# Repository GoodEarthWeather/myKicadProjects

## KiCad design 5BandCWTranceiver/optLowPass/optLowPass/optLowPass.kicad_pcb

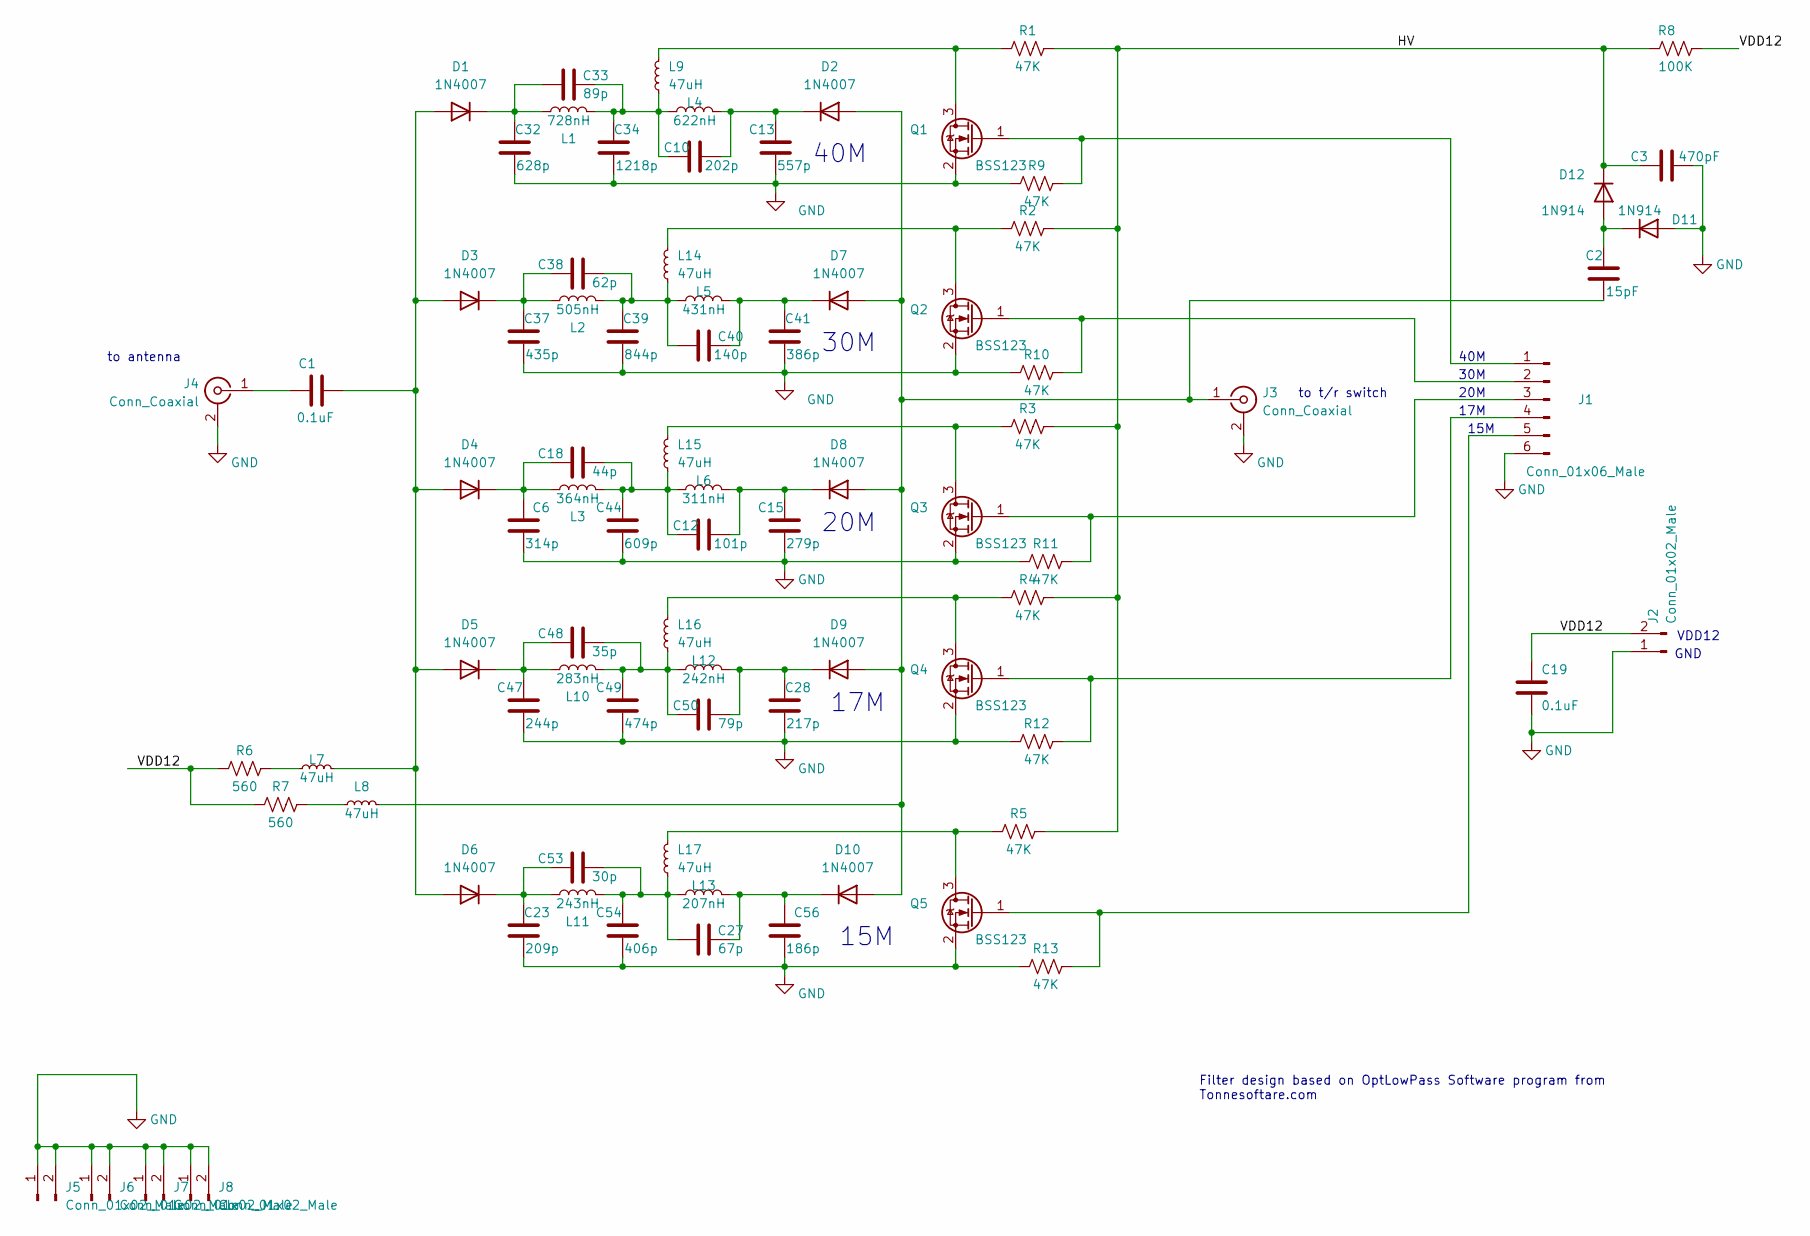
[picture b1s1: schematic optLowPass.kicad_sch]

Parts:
C1: 0.1uF; C_Disc_D4.3mm_W1.9mm_P5.00mm
C2: 15pF; C_Disc_D4.3mm_W1.9mm_P5.00mm
C3: 470pF; C_Disc_D4.3mm_W1.9mm_P5.00mm
C6: 314p; C_1206_3216Metric_Pad1.33x1.80mm_HandSolder
C10: 202p; C_1206_3216Metric_Pad1.33x1.80mm_HandSolder
C12: 101p; C_1206_3216Metric_Pad1.33x1.80mm_HandSolder
C13: 557p; C_1206_3216Metric_Pad1.33x1.80mm_HandSolder
C15: 279p; C_1206_3216Metric_Pad1.33x1.80mm_HandSolder
C18: 44p; C_1206_3216Metric_Pad1.33x1.80mm_HandSolder
C19: 0.1uF; C_0603_1608Metric_Pad1.08x0.95mm_HandSolder
C23: 209p; C_1206_3216Metric_Pad1.33x1.80mm_HandSolder
C27: 67p; C_1206_3216Metric_Pad1.33x1.80mm_HandSolder
C28: 217p; C_1206_3216Metric_Pad1.33x1.80mm_HandSolder
C32: 628p; C_1206_3216Metric_Pad1.33x1.80mm_HandSolder
C33: 89p; C_1206_3216Metric_Pad1.33x1.80mm_HandSolder
C34: 1218p; C_1206_3216Metric_Pad1.33x1.80mm_HandSolder
C37: 435p; C_1206_3216Metric_Pad1.33x1.80mm_HandSolder
C38: 62p; C_1206_3216Metric_Pad1.33x1.80mm_HandSolder
C39: 844p; C_1206_3216Metric_Pad1.33x1.80mm_HandSolder
C40: 140p; C_1206_3216Metric_Pad1.33x1.80mm_HandSolder
C41: 386p; C_1206_3216Metric_Pad1.33x1.80mm_HandSolder
C44: 609p; C_1206_3216Metric_Pad1.33x1.80mm_HandSolder
C47: 244p; C_1206_3216Metric_Pad1.33x1.80mm_HandSolder
C48: 35p; C_1206_3216Metric_Pad1.33x1.80mm_HandSolder
C49: 474p; C_1206_3216Metric_Pad1.33x1.80mm_HandSolder
C50: 79p; C_1206_3216Metric_Pad1.33x1.80mm_HandSolder
C53: 30p; C_1206_3216Metric_Pad1.33x1.80mm_HandSolder
C54: 406p; C_1206_3216Metric_Pad1.33x1.80mm_HandSolder
C56: 186p; C_1206_3216Metric_Pad1.33x1.80mm_HandSolder
D1, D2, D3, D4, D5, D6, D7, D8, D9, D10: 1N4007; D_DO-41_SOD81_P10.16mm_Horizontal
D11, D12: 1N914; D_DO-35_SOD27_P7.62mm_Horizontal
J1: Conn_01x06_Male; PinHeader_1x06_P2.54mm_Vertical
J2, J5, J6, J7, J8: Conn_01x02_Male; PinHeader_1x02_P2.54mm_Vertical
J3, J4: Conn_Coaxial; SMA_Samtec_SMA-J-P-X-ST-EM1_EdgeMount
L1: 728nH; L_Toroid_Vertical_L13.0mm_W6.5mm_P5.60mm
L2: 505nH; L_Toroid_Vertical_L13.0mm_W6.5mm_P5.60mm
L3: 364nH; L_Toroid_Vertical_L13.0mm_W6.5mm_P5.60mm
L4: 622nH; L_Toroid_Vertical_L13.0mm_W6.5mm_P5.60mm
L5: 431nH; L_Toroid_Vertical_L13.0mm_W6.5mm_P5.60mm
L6: 311nH; L_Toroid_Vertical_L13.0mm_W6.5mm_P5.60mm
L7, L8, L9, L14, L15, L16, L17: 47uH; L_Axial_L11.0mm_D4.5mm_P7.62mm_Vertical_Fastron_MECC
L10: 283nH; L_Toroid_Vertical_L13.0mm_W6.5mm_P5.60mm
L11: 243nH; L_Toroid_Vertical_L13.0mm_W6.5mm_P5.60mm
L12: 242nH; L_Toroid_Vertical_L13.0mm_W6.5mm_P5.60mm
L13: 207nH; L_Toroid_Vertical_L13.0mm_W6.5mm_P5.60mm
Q1, Q2, Q3, Q4, Q5: BSS123; SOT-23-3
R1, R2, R3, R4, R5, R9, R10, R11, R12, R13: 47K; R_0603_1608Metric_Pad0.98x0.95mm_HandSolder
R6, R7: 560; R_Axial_DIN0617_L17.0mm_D6.0mm_P20.32mm_Horizontal
R8: 100K; R_0603_1608Metric_Pad0.98x0.95mm_HandSolder

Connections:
/HV: C3.1, D12.1 (K), R1.2, R2.2, R3.2, R4.2, R5.2, R8.2
/VDD12: C19.2, J2.2, R6.1, R7.1, R8.1
GND: C3.2, C6.2, C13.2, C15.2, C19.1, C23.2, C28.2, C32.2, C34.2, C37.2, C39.2, C41.2, C44.2, C47.2, C49.2, C54.2, C56.2, D11.2 (A), J1.6, J2.1, J3.2 (Ext), J4.2 (Ext), J5.1, J5.2, J6.1, J6.2, J7.1, J7.2, J8.1, J8.2, Q1.2 (S), Q2.2 (S), Q3.2 (S), Q4.2 (S), Q5.2 (S), R9.1, R10.1, R11.1, R12.1, R13.1
unnamed: C10.2, C33.1, C34.1, L1.1, L4.2, L9.1
unnamed: C12.2, C18.1, C44.1, L3.1, L6.2, L15.1
unnamed: C27.2, C53.1, C54.1, L11.1, L13.2, L17.1
unnamed: C38.1, C39.1, C40.2, L2.1, L5.2, L14.1
unnamed: C48.1, C49.1, C50.2, L10.1, L12.2, L16.1
unnamed: C1.2, D1.2 (A), D3.2 (A), D4.2 (A), D5.2 (A), D6.2 (A), L7.2
unnamed: C32.1, C33.2, D1.1 (K), L1.2
unnamed: C10.1, C13.1, D2.1 (K), L4.1
unnamed: C37.1, C38.2, D3.1 (K), L2.2
unnamed: C6.1, C18.2, D4.1 (K), L3.2
unnamed: C47.1, C48.2, D5.1 (K), L10.2
unnamed: C23.1, C53.2, D6.1 (K), L11.2
unnamed: C40.1, C41.1, D7.1 (K), L5.1
unnamed: C12.1, C15.1, D8.1 (K), L6.1
unnamed: C28.1, C50.1, D9.1 (K), L12.1
unnamed: C2.2, D2.2 (A), D7.2 (A), D8.2 (A), D9.2 (A), D10.2 (A), J3.1 (In), L8.2
unnamed: C27.1, C56.1, D10.1 (K), L13.1
unnamed: C2.1, D11.1 (K), D12.2 (A)
unnamed: J1.1, Q1.1 (G), R9.2
unnamed: J1.2, Q2.1 (G), R10.2
unnamed: J1.3, Q3.1 (G), R11.2
unnamed: J1.4, Q4.1 (G), R12.2
unnamed: J1.5, Q5.1 (G), R13.2
unnamed: C1.1, J4.1 (In)
unnamed: L7.1, R6.2
unnamed: L8.1, R7.2
unnamed: L9.2, Q1.3 (D), R1.1
unnamed: L14.2, Q2.3 (D), R2.1
unnamed: L15.2, Q3.3 (D), R3.1
unnamed: L16.2, Q4.3 (D), R4.1
unnamed: L17.2, Q5.3 (D), R5.1

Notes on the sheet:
15M
20M
to t/r switch
to antenna
40M
17M
30M
GND
Filter design based on OptLowPass Software program from Tonnesoftare.com
VDD12

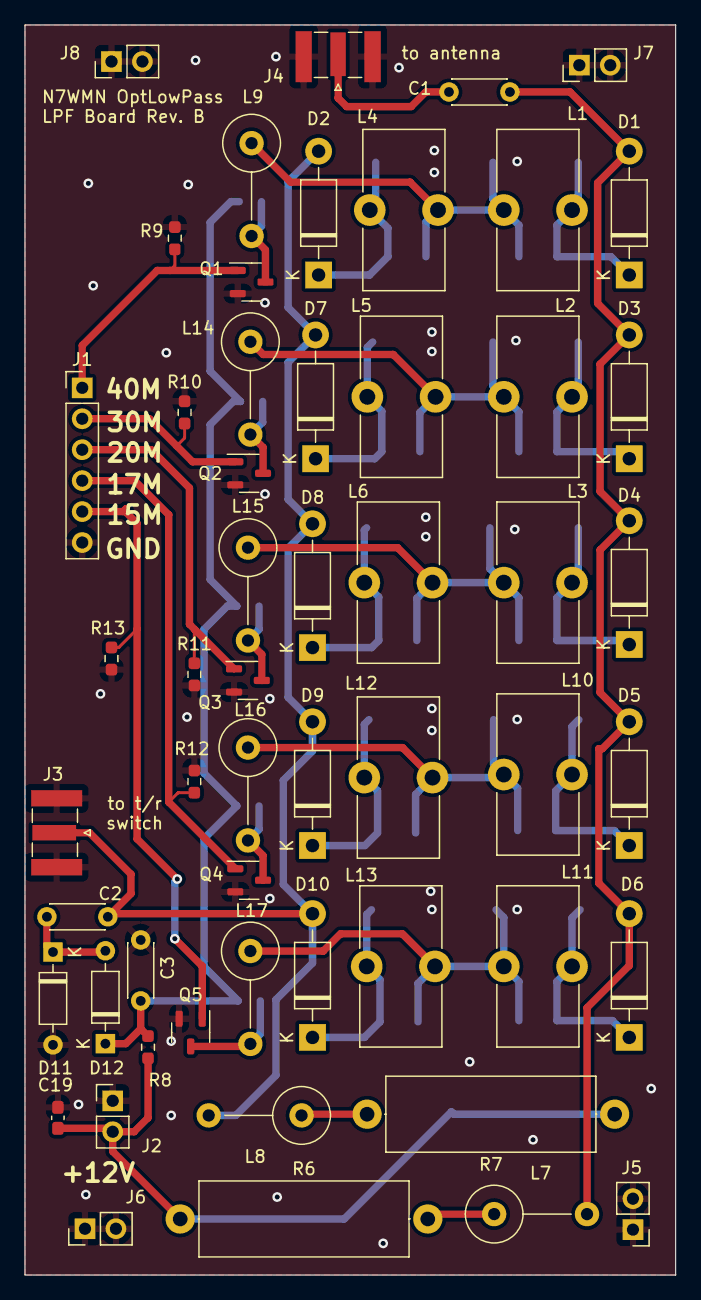
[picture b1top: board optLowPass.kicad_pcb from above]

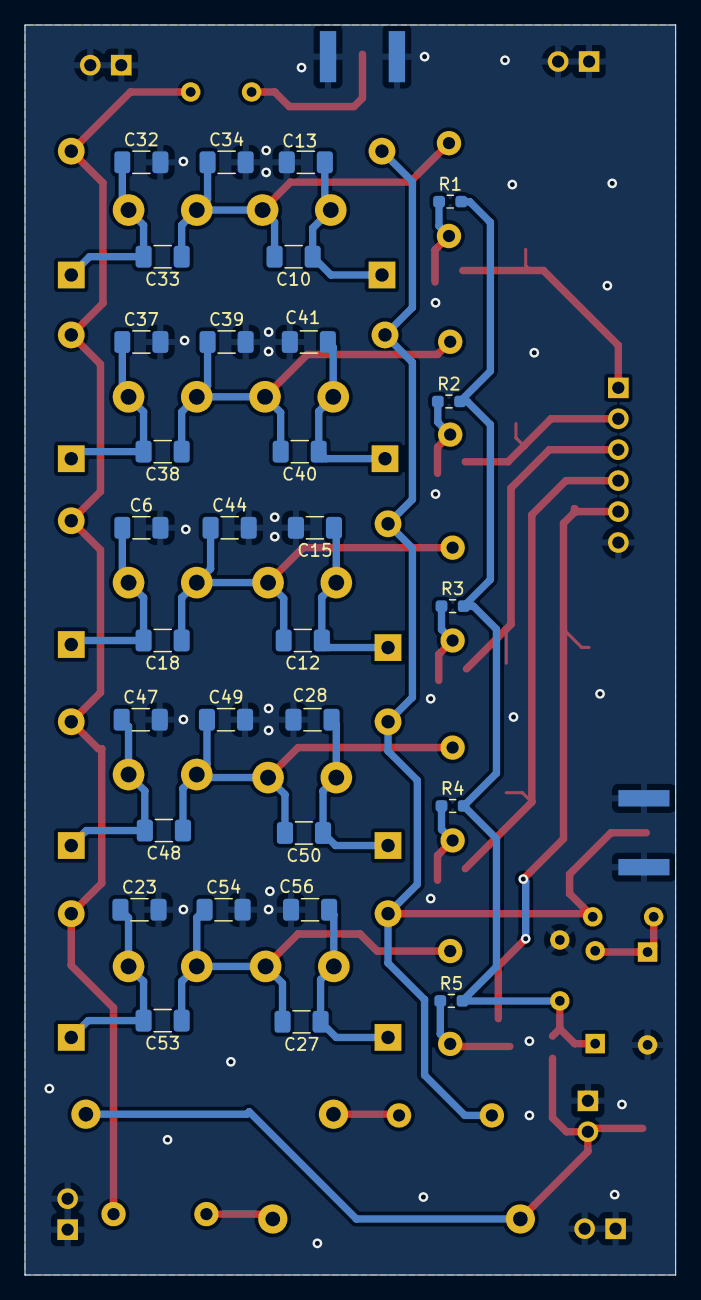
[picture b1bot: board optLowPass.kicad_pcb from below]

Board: 2 copper layers, 53.4 x 102.6 mm, 84 parts (30 on the bottom side), 34 nets.

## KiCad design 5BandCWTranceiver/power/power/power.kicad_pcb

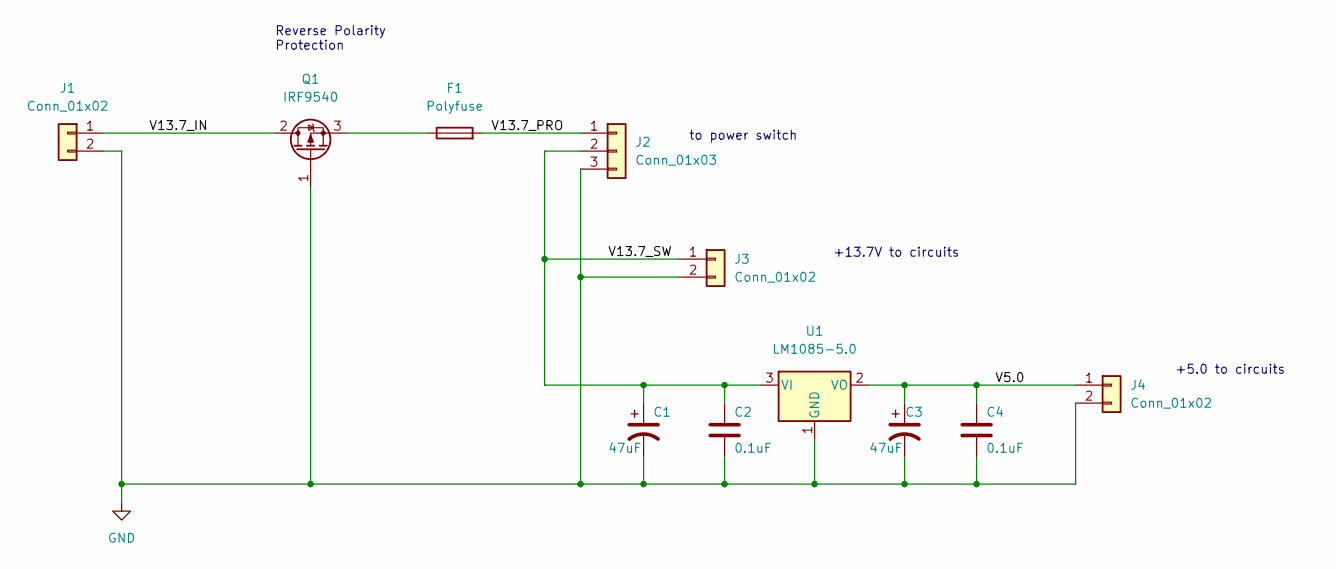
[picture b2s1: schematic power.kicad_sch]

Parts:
C1, C3: 47uF; CP_Radial_D7.5mm_P2.50mm
C2, C4: 0.1uF; C_0603_1608Metric_Pad1.08x0.95mm_HandSolder
F1: Polyfuse; Fuse_2920_7451Metric_Pad2.10x5.45mm_HandSolder
J1, J3, J4: Conn_01x02; SolderWire-0.75sqmm_1x02_P4.8mm_D1.25mm_OD2.3mm
J2: Conn_01x03; SolderWire-0.75sqmm_1x03_P4.8mm_D1.25mm_OD2.3mm
Q1: IRF9540; TO-220-3_Vertical
U1: LM1085-5.0; TO-220-3_Vertical

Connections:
/V5.0: C3.1, C4.1, J4.1, U1.2 (VO)
/V13.7_IN: J1.1, Q1.2 (D)
/V13.7_PRO: F1.2, J2.1
/V13.7_SW: C1.1, C2.1, J2.2, J3.1, U1.3 (VI)
GND: C1.2, C2.2, C3.2, C4.2, J1.2, J2.3, J3.2, J4.2, Q1.1 (G), U1.1 (GND)
unnamed: F1.1, Q1.3 (S)

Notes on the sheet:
+13.7V to circuits
Reverse Polarity Protection
to power switch
+5.0 to circuits

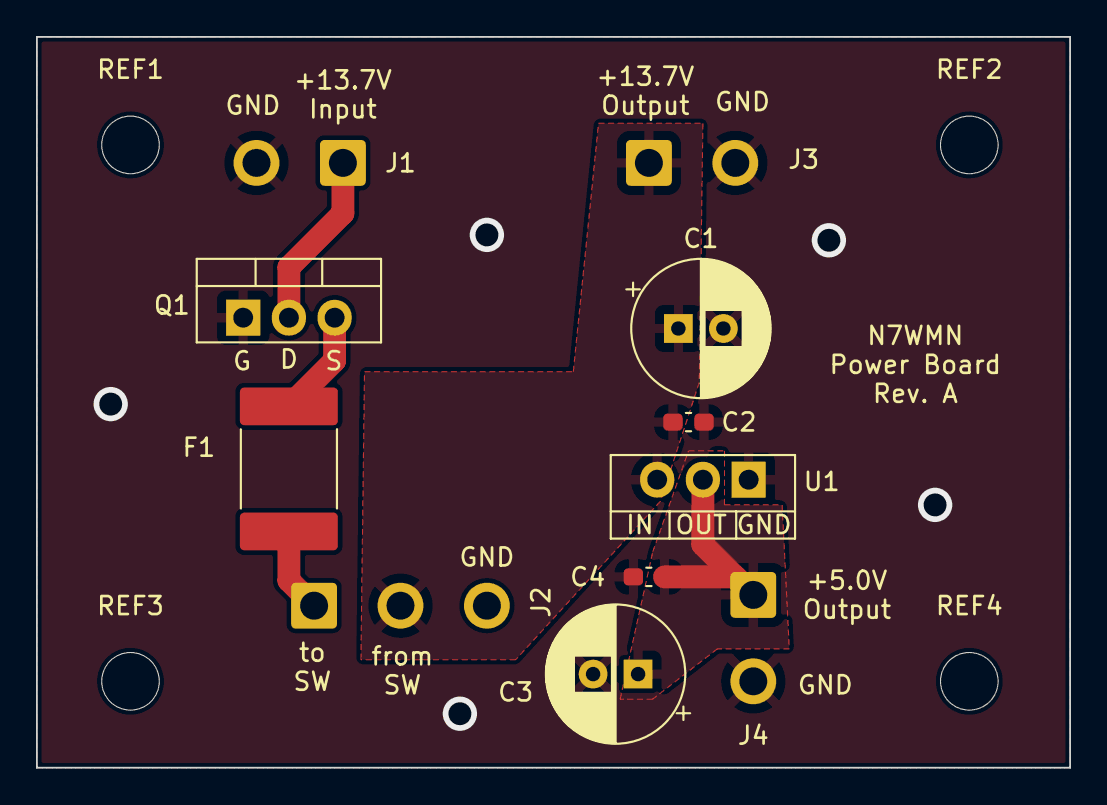
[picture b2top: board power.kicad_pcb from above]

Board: 2 copper layers, 57.4 x 40.6 mm, 15 parts (0 on the bottom side), 6 nets.

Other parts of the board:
REF1, REF2, REF3, REF4: MountingHole_3.2mm_M3

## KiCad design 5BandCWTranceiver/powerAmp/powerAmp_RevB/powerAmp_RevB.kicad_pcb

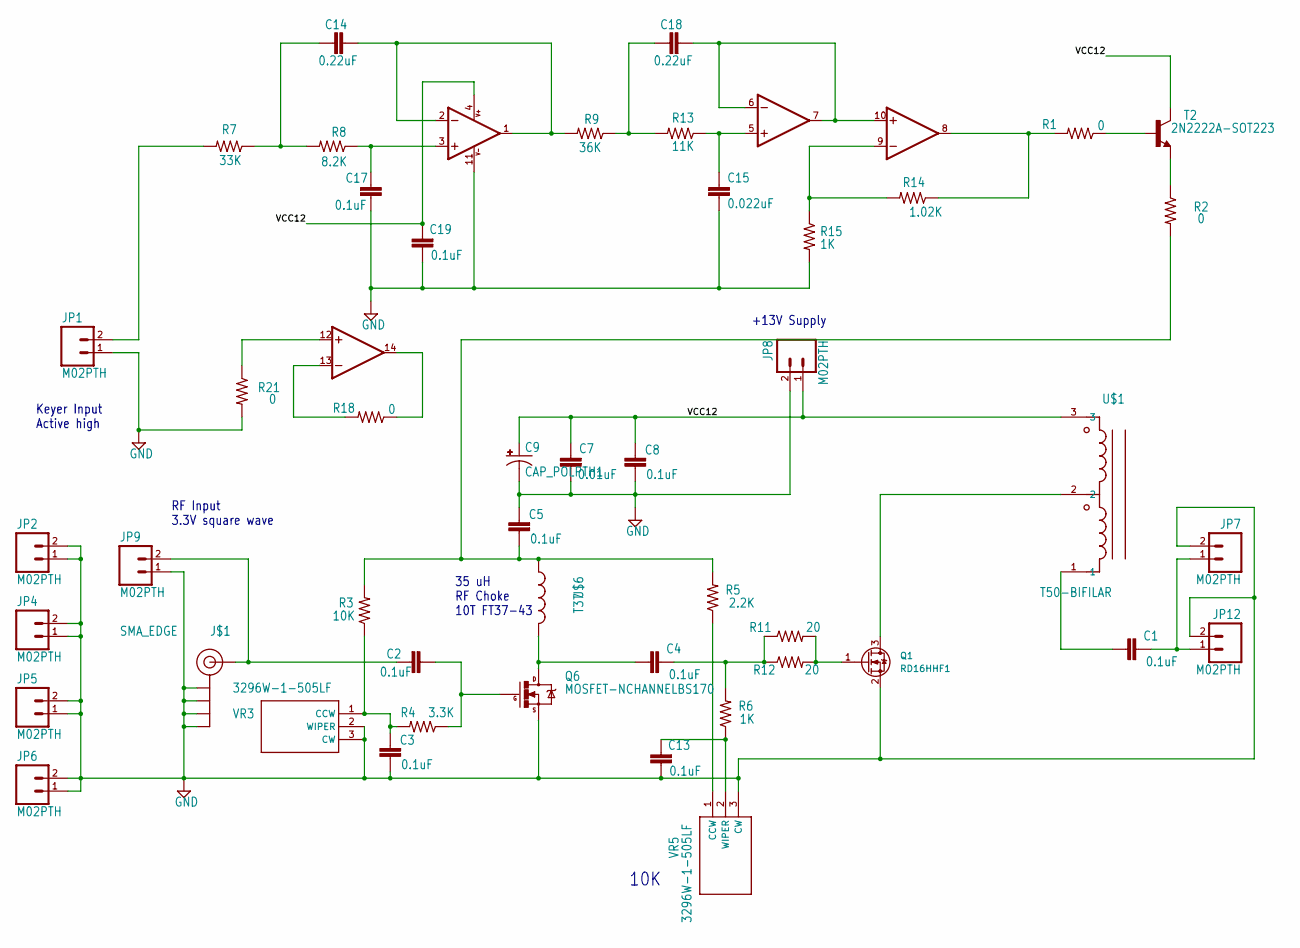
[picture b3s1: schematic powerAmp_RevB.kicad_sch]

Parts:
C1, C4: 0.1uF; CAP-PTH-5MM
C2, C3, C5, C8, C13, C19: 0.1uF; 0603-CAP
C7: 0.01uF; 0603-CAP
C9: CAP_POLPTH1; CPOL-RADIAL-100UF-25V
C14, C18: 710-885012206073; 0603-CAP
C15: 80-C0603C223K3R; 0603-CAP
C17: 710-885012206071; 0603-CAP
J$1: SMA_EDGE; SMA-EDGE
JP1, JP2, JP4, JP5, JP6, JP7, JP8, JP9, JP12: M02PTH; 1X02
Q1: RD16HHF1; TO-220-3_Vertical
Q6: MOSFET-NCHANNELBS170; TO-92
R1, R2, R18, R21: 0; 0603-RES
R3: 10K; 0603-RES
R4: 3.3K; 0603-RES
R5: 2.2K; 0603-RES
R6: 1K; 0603-RES
R7: 603-RC0603FR-0733KL; 0603-RES
R8: 603-RC0603FR-078K2L; 0603-RES
R9: 603-RC0603FR-0736KL; 0603-RES
R11, R12: 20; 1206
R13: 603-RC0603FR-0711KL; 0603-RES
R14: 603-RC0603FR-073KL; 0603-RES
R15: 603-RC0603FR-071KL; 0603-RES
T2: 2N2222A-SOT223; SOT223
U$1: T50-BIFILAR
U$2: OPA1679IDR; SO14
U$6: T37
VR3, VR5: 3296W-1-505LF; 3296W-1

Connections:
/VCC12: C7.2, C8.2, C9.1 (+), C19.2, JP8.1, T2.4 (C), U$1.3, U$2.4 (V+)
GND: C3.1, C5.2, C7.1, C8.1, C9.2 (-), C13.1, C15.2, C17.2, C19.1, J$1.GND@0, J$1.GND@1, J$1.GND@2, J$1.GND@3, JP1.1, JP2.1, JP2.2, JP4.1, JP4.2, JP5.1, JP5.2, JP6.1, JP6.2, JP7.2, JP8.2, JP9.1, JP12.2, Q1.2 (S), Q6.3 (S), R15.2, R21.2, U$2.11 (V-), VR3.2 (WIPER), VR3.3 (CW), VR5.3 (CW)
unnamed: C1.1, U$1.1
unnamed: C1.2, JP7.1, JP12.1
unnamed: C2.1, Q6.2 (G), R4.1
unnamed: C2.2, J$1.SIG (SIGNAL), JP9.2
unnamed: C5.1, R2.2, R3.2, R5.2, U$6.P$1 (1)
unnamed: C13.2, R6.1, VR5.2 (WIPER)
unnamed: C14.1, R7.1, R8.2
unnamed: C14.2, R9.2, U$2.1 (OUT), U$2.2 (-IN)
unnamed: C15.1, R13.1, U$2.5 (+IN)
unnamed: C17.1, R8.1, U$2.3 (+IN)
unnamed: C18.1, R9.1, R13.2
unnamed: C18.2, U$2.6 (-IN), U$2.7 (OUT), U$2.10 (+IN)
unnamed: JP1.2, R7.2
unnamed: C4.1, Q6.1 (D), U$6.P$2 (2)
unnamed: R1.1, T2.1 (B)
unnamed: R1.2, R14.1, U$2.8 (OUT)
unnamed: R2.1, T2.3 (E)
unnamed: C3.2, R3.1, R4.2, VR3.1 (CCW)
unnamed: R5.1, VR5.1 (CCW)
unnamed: C4.2, R6.2, R11.1, R12.1
unnamed: Q1.1 (G), R11.2, R12.2
unnamed: R14.2, R15.1, U$2.9 (-IN)
unnamed: R18.1, U$2.14 (OUT)
unnamed: R18.2, U$2.13 (-IN)
unnamed: R21.1, U$2.12 (+IN)
unnamed: Q1.3 (D), U$1.2

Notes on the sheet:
35 uH RF Choke 10T FT37-43
RF Input 3.3V square wave
10K
+13V Supply
Keyer Input Active high

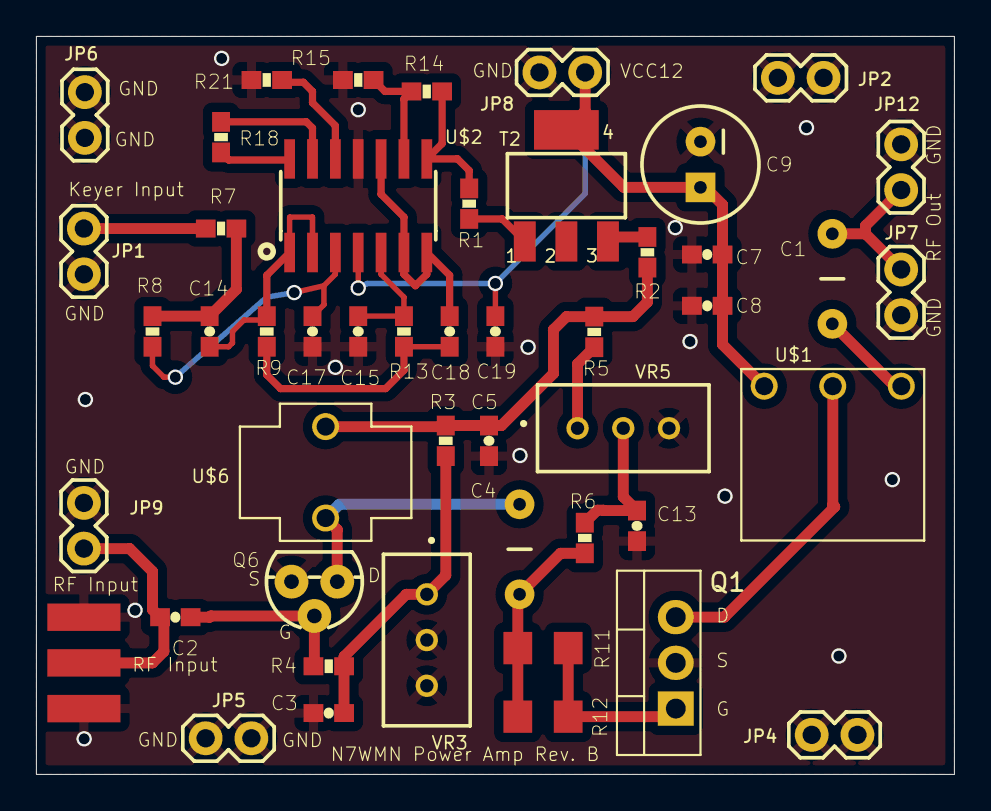
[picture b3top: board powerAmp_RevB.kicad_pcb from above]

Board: 2 copper layers, 51.0 x 41.0 mm, 48 parts (0 on the bottom side), 28 nets.

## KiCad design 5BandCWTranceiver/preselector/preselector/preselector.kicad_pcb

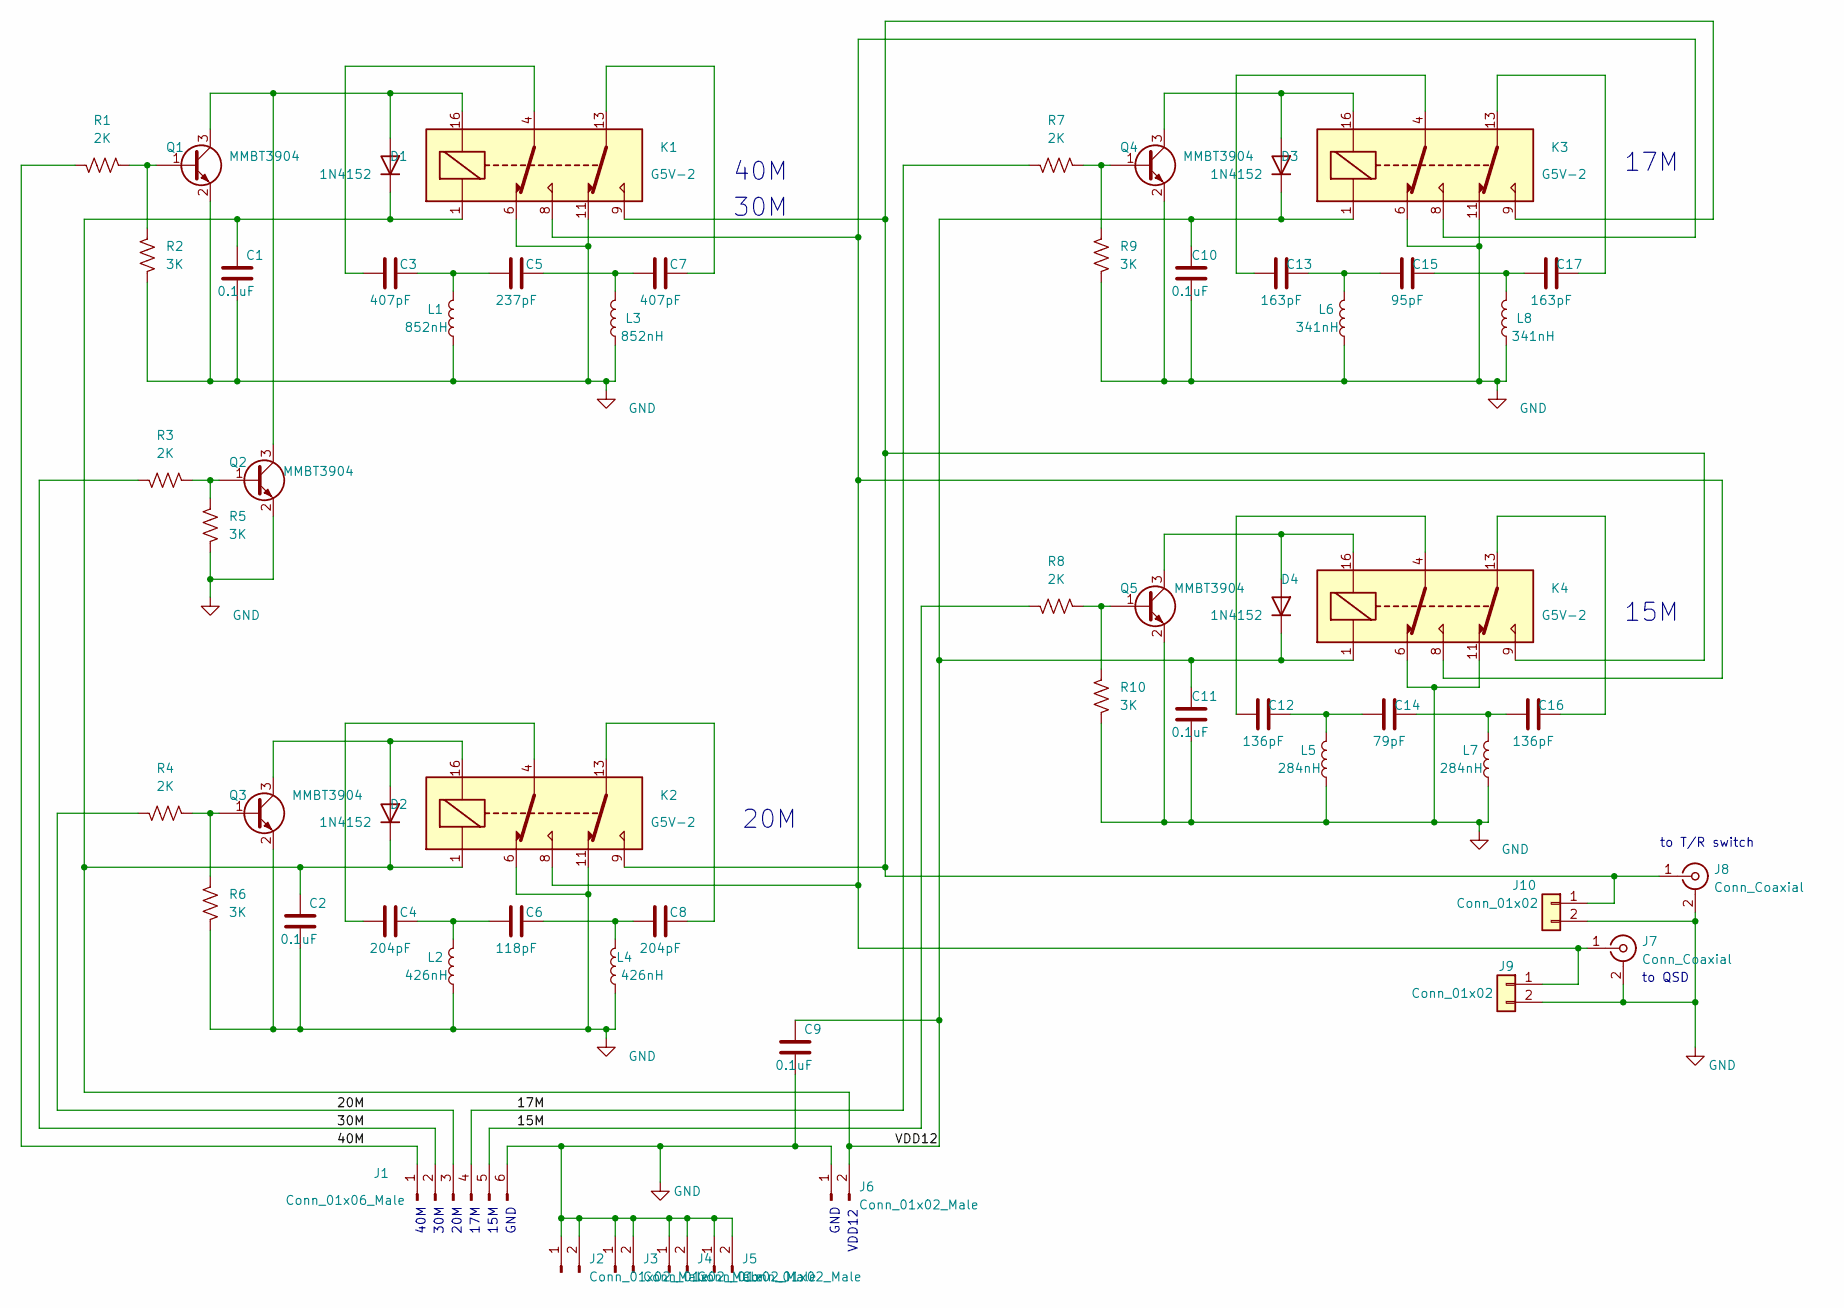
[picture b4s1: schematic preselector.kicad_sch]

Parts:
C1, C2, C9, C10, C11: 0.1uF; C_0603_1608Metric_Pad1.08x0.95mm_HandSolder
C3, C7: 407pF; C_0805_2012Metric_Pad1.18x1.45mm_HandSolder
C4, C8: 204pF; C_0805_2012Metric_Pad1.18x1.45mm_HandSolder
C5: 237pF; C_0805_2012Metric_Pad1.18x1.45mm_HandSolder
C6: 118pF; C_0805_2012Metric_Pad1.18x1.45mm_HandSolder
C12, C16: 136pF; C_0805_2012Metric_Pad1.18x1.45mm_HandSolder
C13, C17: 163pF; C_0805_2012Metric_Pad1.18x1.45mm_HandSolder
C14: 79pF; C_0805_2012Metric_Pad1.18x1.45mm_HandSolder
C15: 95pF; C_0805_2012Metric_Pad1.18x1.45mm_HandSolder
D1, D2, D3, D4: 1N4152; D_DO-41_SOD81_P7.62mm_Horizontal
J1: Conn_01x06_Male; PinHeader_1x06_P2.54mm_Vertical
J2, J3, J4, J5, J6: Conn_01x02_Male; PinHeader_1x02_P2.54mm_Vertical
J7, J8: Conn_Coaxial; SMA_Samtec_SMA-J-P-X-ST-EM1_EdgeMount
J9, J10: Conn_01x02; PinHeader_1x02_P2.54mm_Vertical
K1, K2, K3, K4: G5V-2; Relay_DPDT_Omron_G5V-2
L1, L3: 852nH; L_Toroid_Vertical_L13.0mm_W6.5mm_P5.60mm
L2, L4: 426nH; L_Toroid_Vertical_L13.0mm_W6.5mm_P5.60mm
L5, L7: 284nH; L_Toroid_Vertical_L13.0mm_W6.5mm_P5.60mm
L6, L8: 341nH; L_Toroid_Vertical_L13.0mm_W6.5mm_P5.60mm
Q1, Q2, Q3, Q4, Q5: MMBT3904; SOT-23
R1, R3, R4, R7, R8: 2K; R_0603_1608Metric_Pad0.98x0.95mm_HandSolder
R2, R5, R6, R9, R10: 3K; R_0603_1608Metric_Pad0.98x0.95mm_HandSolder

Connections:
/15M: J1.5, R8.2
/17M: J1.4, R7.2
/20M: J1.3, R4.2
/30M: J1.2, R3.2
/40M: J1.1, R1.2
/VDD12: C1.1, C2.1, C9.1, C10.1, C11.1, D1.1 (K), D2.1 (K), D3.1 (K), D4.1 (K), J6.2, K1.1, K2.1, K3.1, K4.1
GND: C1.2, C2.2, C9.2, C10.2, C11.2, J1.6, J2.1, J2.2, J3.1, J3.2, J4.1, J4.2, J5.1, J5.2, J6.1, J7.2 (Ext), J8.2 (Ext), J9.2, J10.2, K1.6, K1.11, K2.6, K2.11, K3.6, K3.11, K4.6, K4.11, L1.2, L2.2, L3.2, L4.2, L5.2, L6.2, L7.2, L8.2, Q1.2 (E), Q2.2 (E), Q3.2 (E), Q4.2 (E), Q5.2 (E), R2.2, R5.2, R6.2, R9.2, R10.2
unnamed: C3.1, C5.2, L1.1
unnamed: C3.2, K1.4
unnamed: C4.1, C6.2, L2.1
unnamed: C4.2, K2.4
unnamed: C5.1, C7.2, L3.1
unnamed: C6.1, C8.2, L4.1
unnamed: C7.1, K1.13
unnamed: C8.1, K2.13
unnamed: C12.1, C14.2, L5.1
unnamed: C12.2, K4.4
unnamed: C13.1, C15.2, L6.1
unnamed: C13.2, K3.4
unnamed: C14.1, C16.2, L7.1
unnamed: C15.1, C17.2, L8.1
unnamed: C16.1, K4.13
unnamed: C17.1, K3.13
unnamed: D1.2 (A), K1.16, Q1.3 (C), Q2.3 (C)
unnamed: D2.2 (A), K2.16, Q3.3 (C)
unnamed: D3.2 (A), K3.16, Q4.3 (C)
unnamed: D4.2 (A), K4.16, Q5.3 (C)
unnamed: J7.1 (In), J9.1, K1.8, K2.8, K3.8, K4.8
unnamed: J8.1 (In), J10.1, K1.9, K2.9, K3.9, K4.9
unnamed: Q1.1 (B), R1.1, R2.1
unnamed: Q2.1 (B), R3.1, R5.1
unnamed: Q3.1 (B), R4.1, R6.1
unnamed: Q4.1 (B), R7.1, R9.1
unnamed: Q5.1 (B), R8.1, R10.1

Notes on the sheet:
15M
20M
to QSD
GND
to T/R switch
40M
17M
30M
VDD12

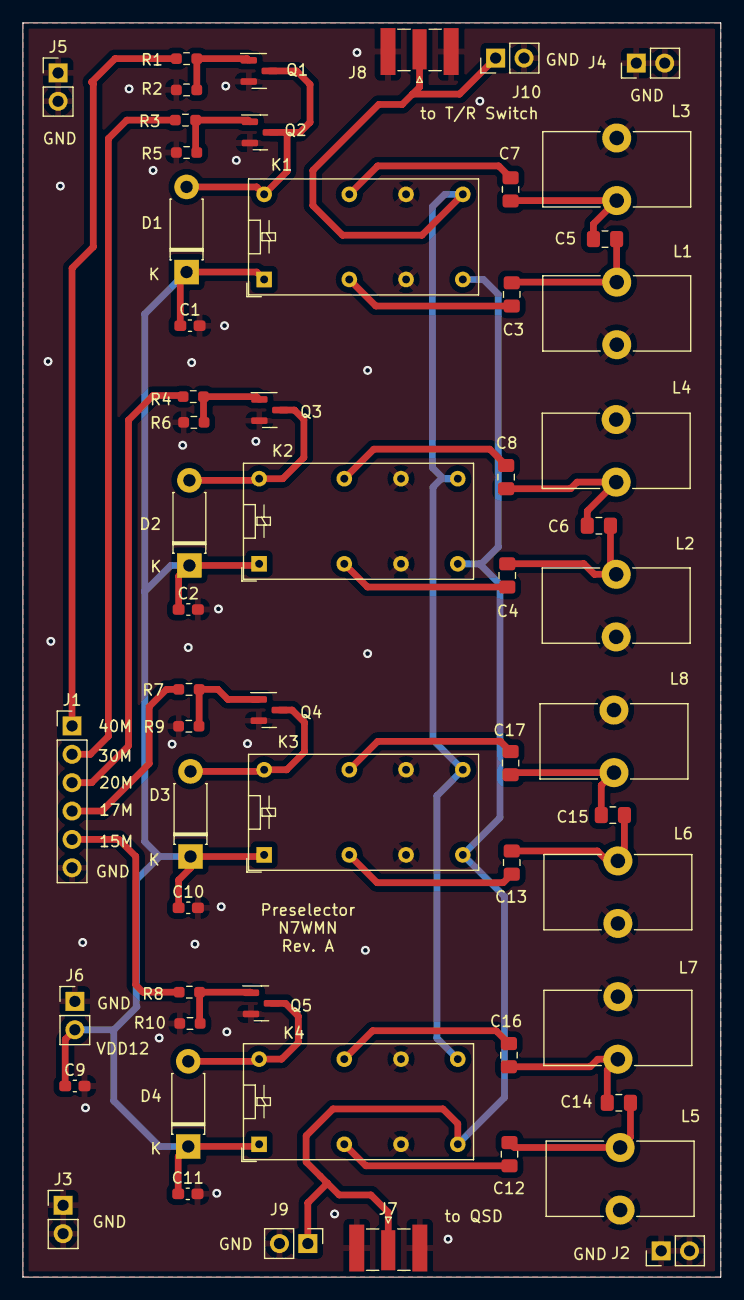
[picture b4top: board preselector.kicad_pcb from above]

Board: 2 copper layers, 62.5 x 112.3 mm, 58 parts (0 on the bottom side), 34 nets.

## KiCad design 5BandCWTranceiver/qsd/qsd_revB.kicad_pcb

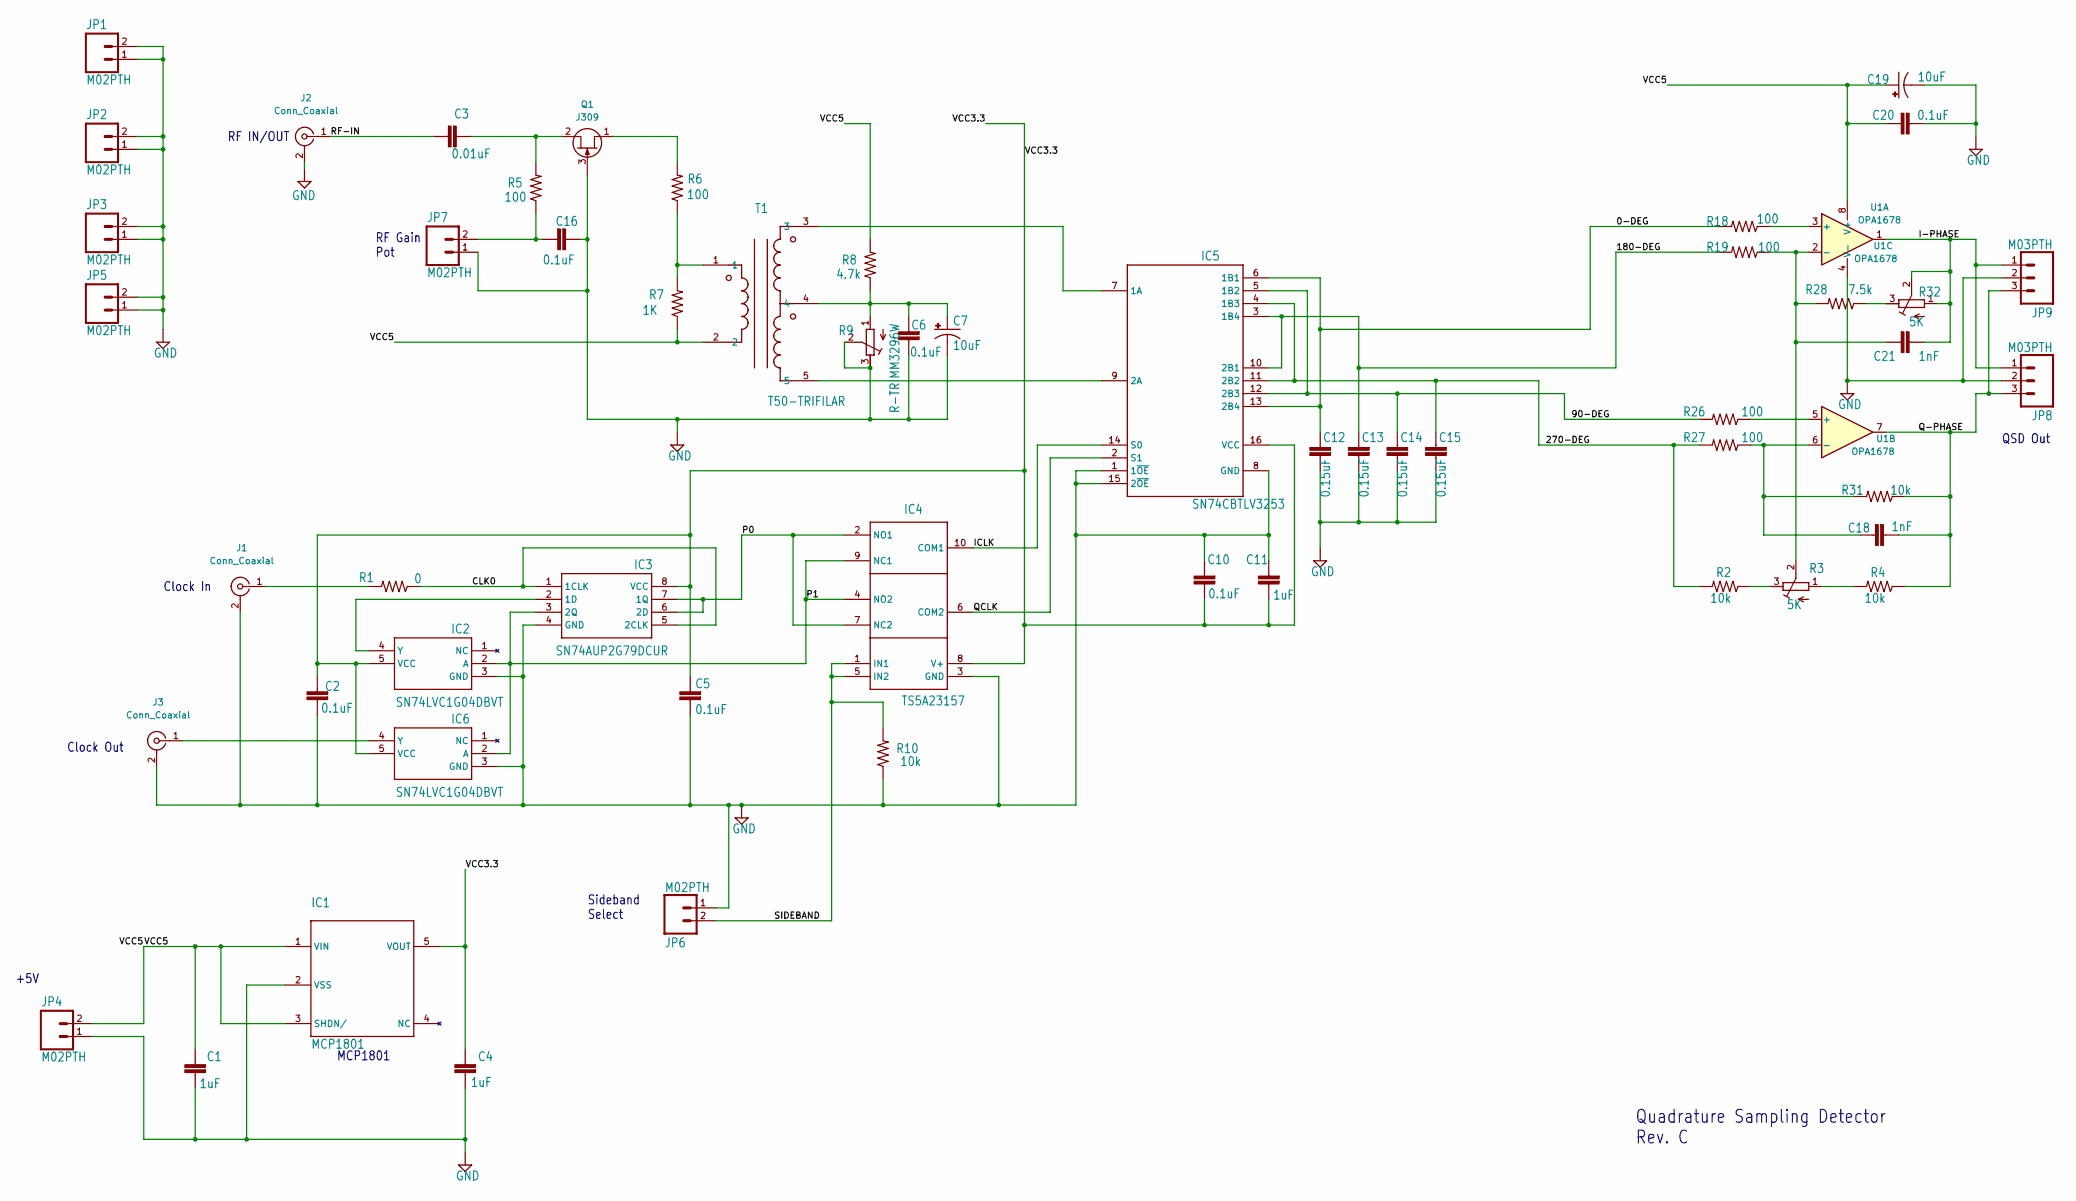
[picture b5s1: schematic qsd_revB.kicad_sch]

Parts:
C1, C4, C11: 1uF; 0603-CAP
C2, C5, C6, C10, C16, C20: 0.1uF; C_0603_1608Metric_Pad1.08x0.95mm_HandSolder
C3: 0.01uF; C_0603_1608Metric_Pad1.08x0.95mm_HandSolder
C7, C19: 10uF; CPOL-RADIAL-10UF-25V
C12, C13, C14, C15: 0.15uF; C_0603_1608Metric_Pad1.08x0.95mm_HandSolder
C18, C21: 1nF; C_0603_1608Metric_Pad1.08x0.95mm_HandSolder
IC1: MCP1801; SOT23-5
IC2, IC6: SN74LVC1G04DBVT; SOT95P280X145-5N
IC3: SN74AUP2G79DCUR; SOP50P310X90-8N
IC4: TS5A23157; MSOP10
IC5: SN74CBTLV3253; TSSOP16
J1, J2, J3: Conn_Coaxial; SMA_Samtec_SMA-J-P-X-ST-EM1_EdgeMount
JP1, JP2, JP3, JP4, JP5, JP6, JP7: M02PTH; 1X02
JP8, JP9: M03PTH; 1X03
Q1: J309; SOT-23
R1: 0; R_0603_1608Metric_Pad0.98x0.95mm_HandSolder
R2, R4, R10, R31: 10k; R_0603_1608Metric_Pad0.98x0.95mm_HandSolder
R3, R32: 5K; RTRIM3296W
R5, R6, R18, R19, R26, R27: 100; R_0603_1608Metric_Pad0.98x0.95mm_HandSolder
R7: 1K; R_0603_1608Metric_Pad0.98x0.95mm_HandSolder
R8: 4.7k; R_0603_1608Metric_Pad0.98x0.95mm_HandSolder
R9: R-TRIMM3296W; RTRIM3296W
R28: 7.5k; R_0603_1608Metric_Pad0.98x0.95mm_HandSolder
T1: T50-TRIFILAR
U1: OPA1678; SOIC-8_3.9x4.9mm_P1.27mm

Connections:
/0-DEG: C12.2, IC5.6 (1B1), IC5.13 (2B4), R18.2
/90-DEG: C14.2, IC5.5 (1B2), IC5.12 (2B3), R26.2
/180-DEG: C13.2, IC5.3 (1B4), IC5.10 (2B1), R19.2
/270-DEG: C15.2, IC5.4 (1B3), IC5.11 (2B2), R2.2, R27.2
/CLK0: IC3.1 (1CLK), IC3.5 (2CLK), R1.1
/I-PHASE: C21.1, JP8.1, JP9.1, R32.1 (A), R32.2 (S), U1.1
/ICLK: IC4.10 (COM1), IC5.14 (S0)
/P0: IC3.6 (2D), IC3.7 (1Q), IC4.2 (NO1), IC4.7 (NC2)
/P1: IC2.2 (A), IC3.3 (2Q), IC4.4 (NO2), IC4.9 (NC1), IC6.2 (A)
/Q-PHASE: C18.1, JP8.3, JP9.3, R4.1, R31.1, U1.7
/QCLK: IC4.6 (COM2), IC5.2 (S1)
/RF-IN: C3.2, J2.1 (In)
/SIDEBAND: IC4.1 (IN1), IC4.5 (IN2), JP6.2, R10.2
/VCC3.3: C2.2, C4.2, C5.2, C10.1, C11.1, IC1.5 (VOUT), IC2.5 (VCC), IC3.8 (VCC), IC4.8 (V+), IC5.16 (VCC), IC6.5 (VCC)
/VCC5: C1.2, C19.1 (+), C20.2, IC1.1 (VIN), IC1.3 (SHDN/), JP4.2, R7.1, R8.2, T1.2, U1.8 (V+)
GND: C1.1, C2.1, C4.1, C5.1, C6.1, C7.2 (-), C10.2, C11.2, C12.1, C13.1, C14.1, C15.1, C16.1, C19.2 (-), C20.1, IC1.2 (VSS), IC2.3 (GND), IC3.4 (GND), IC4.3 (GND), IC5.1 (1~OE), IC5.8 (GND), IC5.15 (2~OE), IC6.3 (GND), J1.2 (Ext), J2.2 (Ext), J3.2 (Ext), JP1.1, JP1.2, JP2.1, JP2.2, JP3.1, JP3.2, JP4.1, JP5.1, JP5.2, JP6.1, JP7.1, JP8.2, JP9.2, Q1.3 (G), R9.2 (S), R9.3 (E), R10.1, U1.4 (V-)
unnamed: C3.1, Q1.2 (S), R5.2
unnamed: C6.2, C7.1 (+), R8.1, R9.1 (A), T1.4
unnamed: C18.2, R27.1, R31.2, U1.6 (-)
unnamed: C21.2, R3.2 (S), R19.1, R28.2, U1.2 (-)
unnamed: IC2.4 (Y), IC3.2 (1D)
unnamed: IC5.7 (1A), T1.3
unnamed: IC5.9 (2A), T1.5
unnamed: IC6.4 (Y), J3.1 (In)
unnamed: J1.1 (In), R1.2
unnamed: R2.1, R3.3 (E)
unnamed: R3.1 (A), R4.2
unnamed: C16.2, JP7.2, R5.1
unnamed: R6.1, R7.2, T1.1
unnamed: Q1.1 (D), R6.2
unnamed: R18.1, U1.3 (+)
unnamed: R26.1, U1.5 (+)
unnamed: R28.1, R32.3 (E)

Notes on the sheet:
Clock In
RF Gain Pot
Sideband Select
MCP1801
Clock Out
QSD Out
RF IN/OUT
+5V
Quadrature Sampling Detector Rev. C

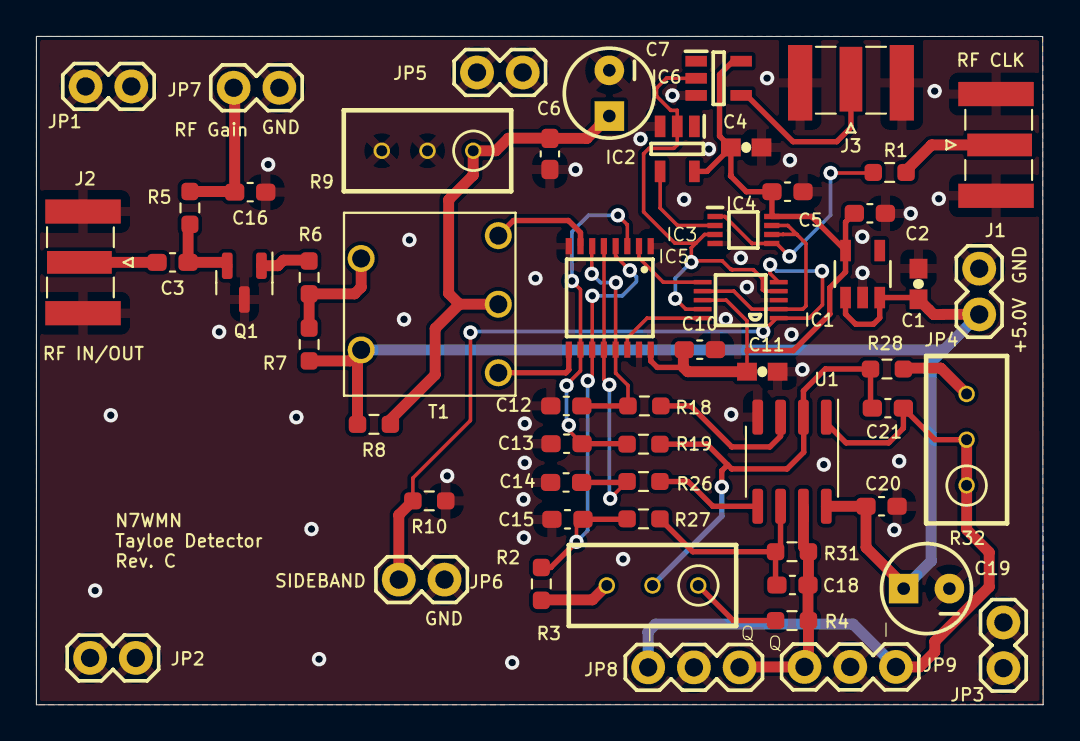
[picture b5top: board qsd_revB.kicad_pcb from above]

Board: 2 copper layers, 55.9 x 37.1 mm, 56 parts (0 on the bottom side), 33 nets.
